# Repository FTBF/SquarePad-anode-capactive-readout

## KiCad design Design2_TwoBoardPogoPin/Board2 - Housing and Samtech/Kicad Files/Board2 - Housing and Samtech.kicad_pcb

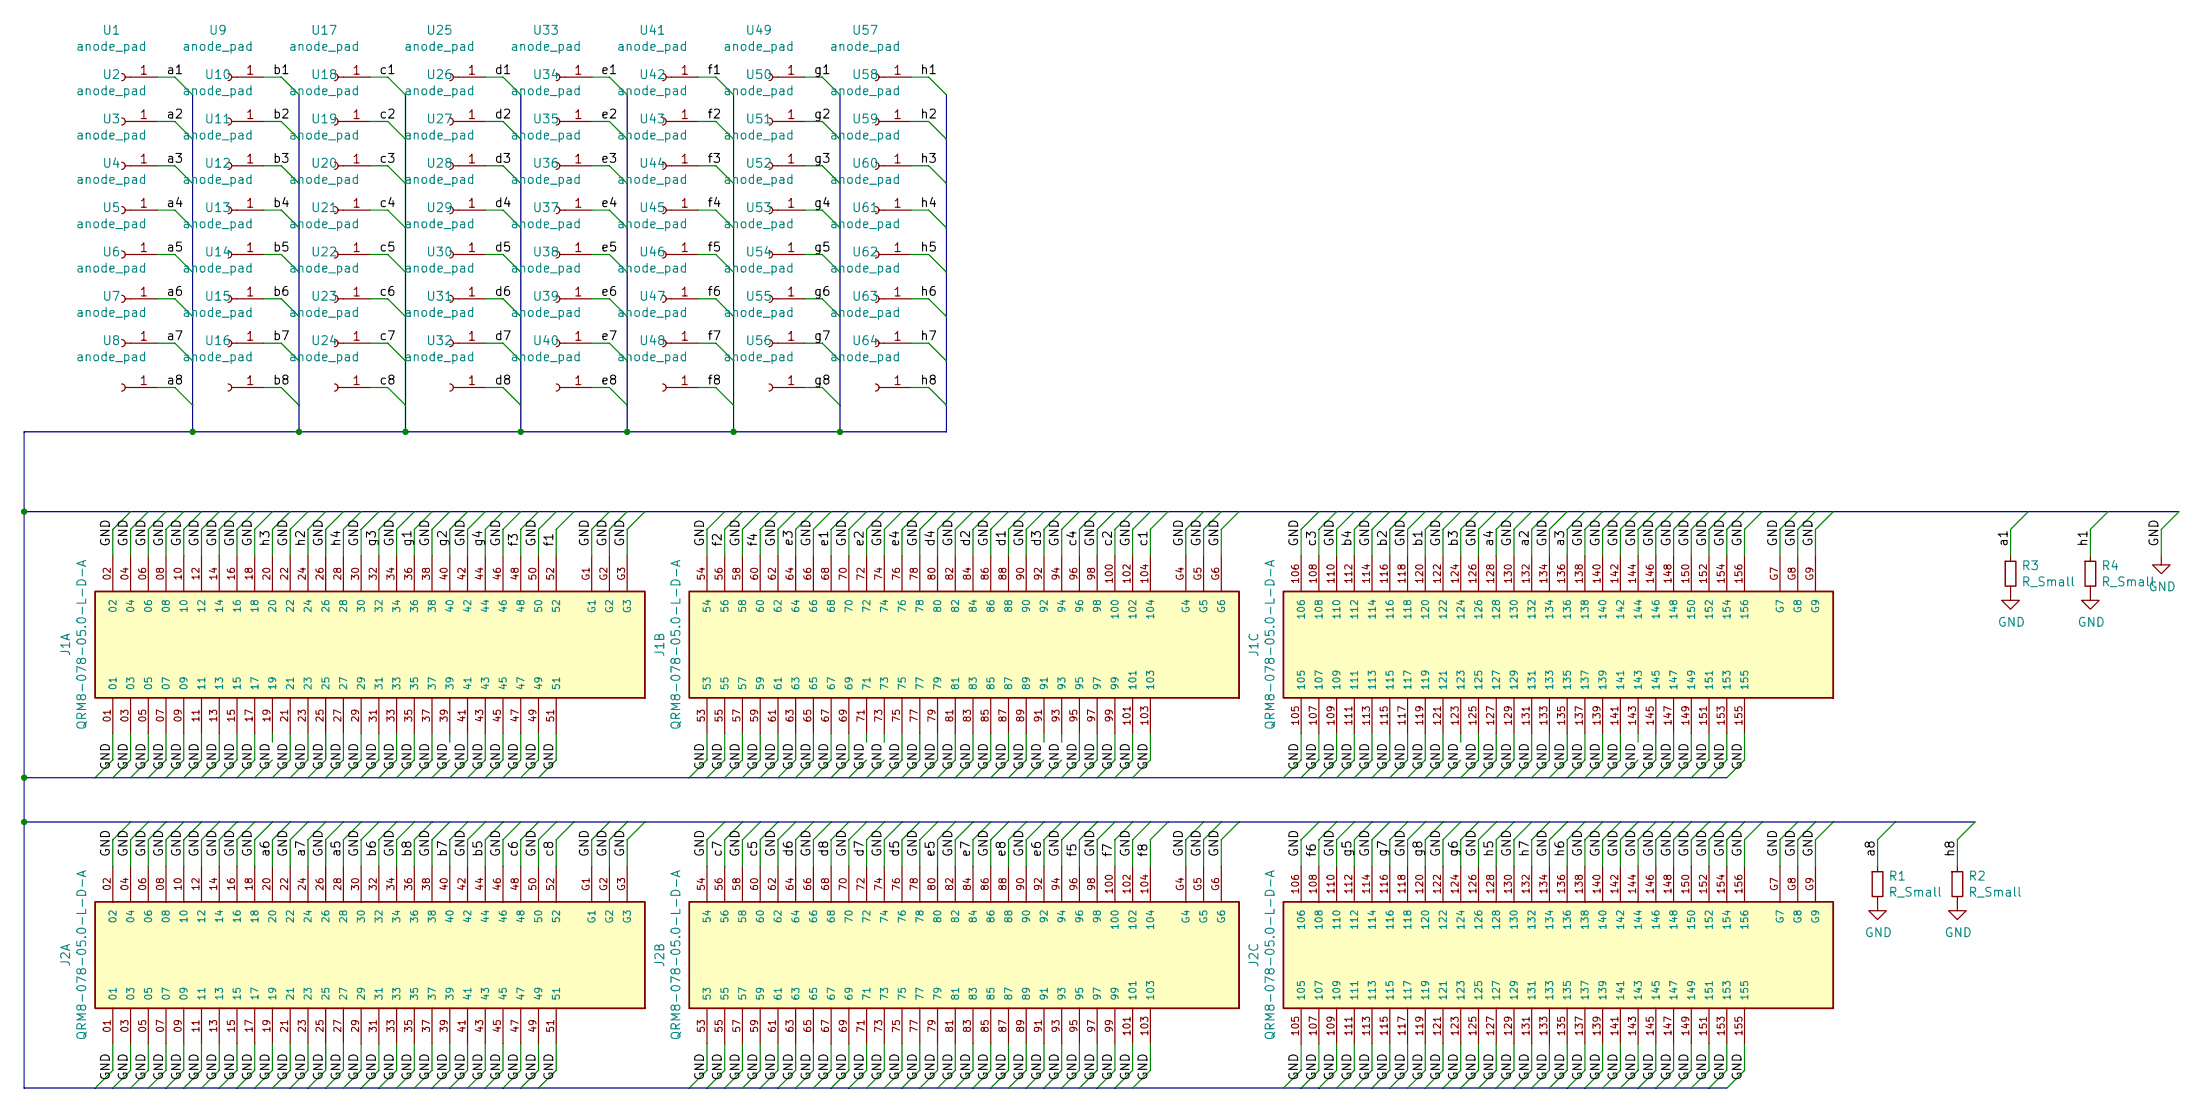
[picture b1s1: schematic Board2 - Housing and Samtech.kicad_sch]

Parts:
J1, J2: QRM8-078-05.0-L-D-A; SAMTEC_QRM8-078-05.0-L-D-A
R1, R2, R3, R4: R_Small; R_0805_2012Metric_Pad1.20x1.40mm_HandSolder
U1, U2, U3, U4, U5, U6, U7, U8, U9, U10, U11, U12, U13, U14, U15, U16, U17, U18, U19, U20, U21, U22, U23, U24, U25, U26, U27, U28, U29, U30, U31, U32, U33, U34, U35, U36, U37, U38, U39, U40, U41, U42, U43, U44, U45, U46, U47, U48, U49, U50, U51, U52, U53, U54, U55, U56, U57, U58, U59, U60, U61, U62, U63, U64: anode_pad; Pin_D0.7mm_L6.5mm_W1.8mm_FlatFork

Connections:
/a1: R3.1, U1.1
/a2: J1.132, U2.1
/a3: J1.136, U3.1
/a4: J1.128, U4.1
/a5: J2.28, U5.1
/a6: J2.20, U6.1
/a7: J2.24, U7.1
/a8: R1.1, U8.1
/b1: J1.120, U9.1
/b2: J1.116, U10.1
/b3: J1.124, U11.1
/b4: J1.112, U12.1
/b5: J2.44, U13.1
/b6: J2.32, U14.1
/b7: J2.40, U15.1
/b8: J2.36, U16.1
/c1: J1.104, U17.1
/c2: J1.100, U18.1
/c3: J1.108, U19.1
/c4: J1.96, U20.1
/c5: J2.60, U21.1
/c6: J2.48, U22.1
/c7: J2.56, U23.1
/c8: J2.52, U24.1
/d1: J1.88, U25.1
/d2: J1.84, U26.1
/d3: J1.92, U27.1
/d4: J1.80, U28.1
/d5: J2.76, U29.1
/d6: J2.64, U30.1
/d7: J2.72, U31.1
/d8: J2.68, U32.1
/e1: J1.68, U33.1
/e2: J1.72, U34.1
/e3: J1.64, U35.1
/e4: J1.76, U36.1
/e5: J2.80, U37.1
/e6: J2.92, U38.1
/e7: J2.84, U39.1
/e8: J2.88, U40.1
/f1: J1.52, U41.1
/f2: J1.56, U42.1
/f3: J1.48, U43.1
/f4: J1.60, U44.1
/f5: J2.96, U45.1
/f6: J2.108, U46.1
/f7: J2.100, U47.1
/f8: J2.104, U48.1
/g1: J1.36, U49.1
/g2: J1.40, U50.1
/g3: J1.32, U51.1
/g4: J1.44, U52.1
/g5: J2.112, U53.1
/g6: J2.124, U54.1
/g7: J2.116, U55.1
/g8: J2.120, U56.1
/h1: R4.1, U57.1
/h2: J1.24, U58.1
/h3: J1.20, U59.1
/h4: J1.28, U60.1
/h5: J2.128, U61.1
/h6: J2.136, U62.1
/h7: J2.132, U63.1
/h8: R2.1, U64.1
GND: J1.01, J1.02, J1.03, J1.04, J1.05, J1.06, J1.07, J1.08, J1.09, J1.10, J1.11, J1.12, J1.13, J1.14, J1.15, J1.16, J1.17, J1.18, J1.19, J1.21, J1.22, J1.23, J1.25, J1.26, J1.27, J1.29, J1.30, J1.31, J1.33, J1.34, J1.35, J1.37, J1.38, J1.39, J1.41, J1.42, J1.43, J1.45, J1.46, J1.47, J1.49, J1.50, J1.51, J1.53, J1.54, J1.55, J1.57, J1.58, J1.59, J1.61, J1.62, J1.63, J1.65, J1.66, J1.67, J1.69, J1.70, J1.71, J1.73, J1.74, J1.75, J1.77, J1.78, J1.79, J1.81, J1.82, J1.83, J1.85, J1.86, J1.87, J1.89, J1.90, J1.91, J1.93, J1.94, J1.95, J1.97, J1.98, J1.99, J1.101, J1.102, J1.103, J1.105, J1.106, J1.107, J1.109, J1.110, J1.111, J1.113, J1.114, J1.115, J1.117, J1.118, J1.119, J1.121, J1.122, J1.123, J1.125, J1.126, J1.127, J1.129, J1.130, J1.131, J1.133, J1.134, J1.135, J1.137, J1.138, J1.139, J1.140, J1.141, J1.142, J1.143, J1.144, J1.145, J1.146, J1.147, J1.148, J1.149, J1.150, J1.151, J1.152, J1.153, J1.154, J1.155, J1.156, J1.G1, J1.G2, J1.G3, J1.G4, J1.G5, J1.G6, J1.G7, J1.G8, J1.G9, J2.01, J2.02, J2.03, J2.04, J2.05, J2.06, J2.07, J2.08, J2.09, J2.10, J2.11, J2.12, J2.13, J2.14, J2.15, J2.16, J2.17, J2.18, J2.19, J2.21, J2.22, J2.23, J2.25, J2.26, J2.27, J2.29, J2.30, J2.31, J2.33, J2.34, J2.35, J2.37, J2.38, J2.39, J2.41, J2.42, J2.43, J2.45, J2.46, J2.47, J2.49, J2.50, J2.51, J2.53, J2.54, J2.55, J2.57, J2.58, J2.59, J2.61, J2.62, J2.63, J2.65, J2.66, J2.67, J2.69, J2.70, J2.71, J2.73, J2.74, J2.75, J2.77, J2.78, J2.79, J2.81, J2.82, J2.83, J2.85, J2.86, J2.87, J2.89, J2.90, J2.91, J2.93, J2.94, J2.95, J2.97, J2.98, J2.99, J2.101, J2.102, J2.103, J2.105, J2.106, J2.107, J2.109, J2.110, J2.111, J2.113, J2.114, J2.115, J2.117, J2.118, J2.119, J2.121, J2.122, J2.123, J2.125, J2.126, J2.127, J2.129, J2.130, J2.131, J2.133, J2.134, J2.135, J2.137, J2.138, J2.139, J2.140, J2.141, J2.142, J2.143, J2.144, J2.145, J2.146, J2.147, J2.148, J2.149, J2.150, J2.151, J2.152, J2.153, J2.154, J2.155, J2.156, J2.G1, J2.G2, J2.G3, J2.G4, J2.G5, J2.G6, J2.G7, J2.G8, J2.G9, R1.2, R2.2, R3.2, R4.2

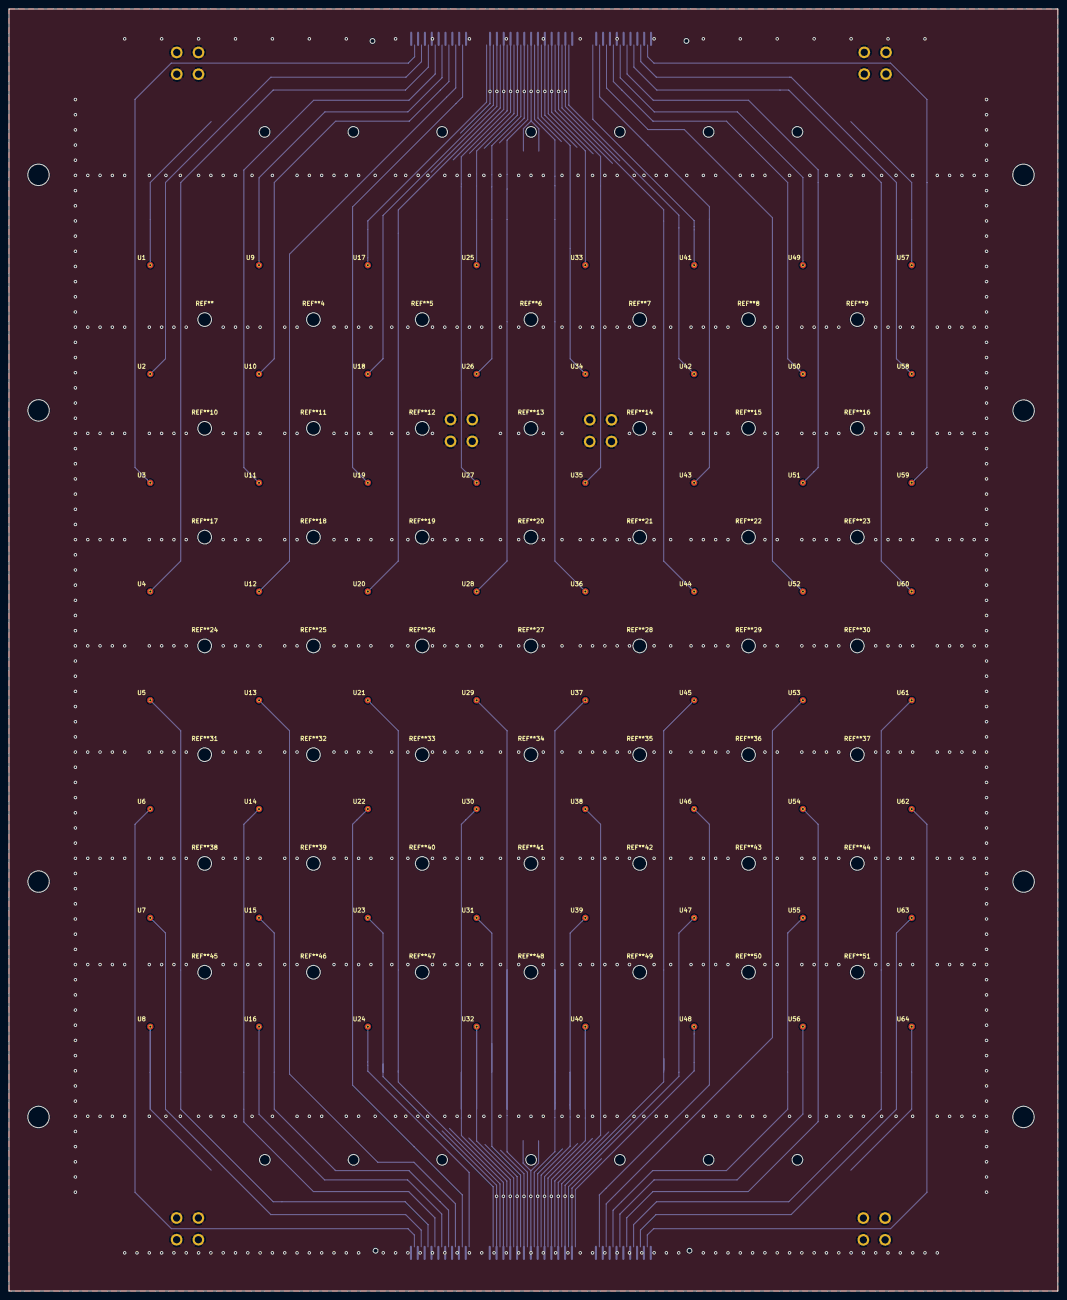
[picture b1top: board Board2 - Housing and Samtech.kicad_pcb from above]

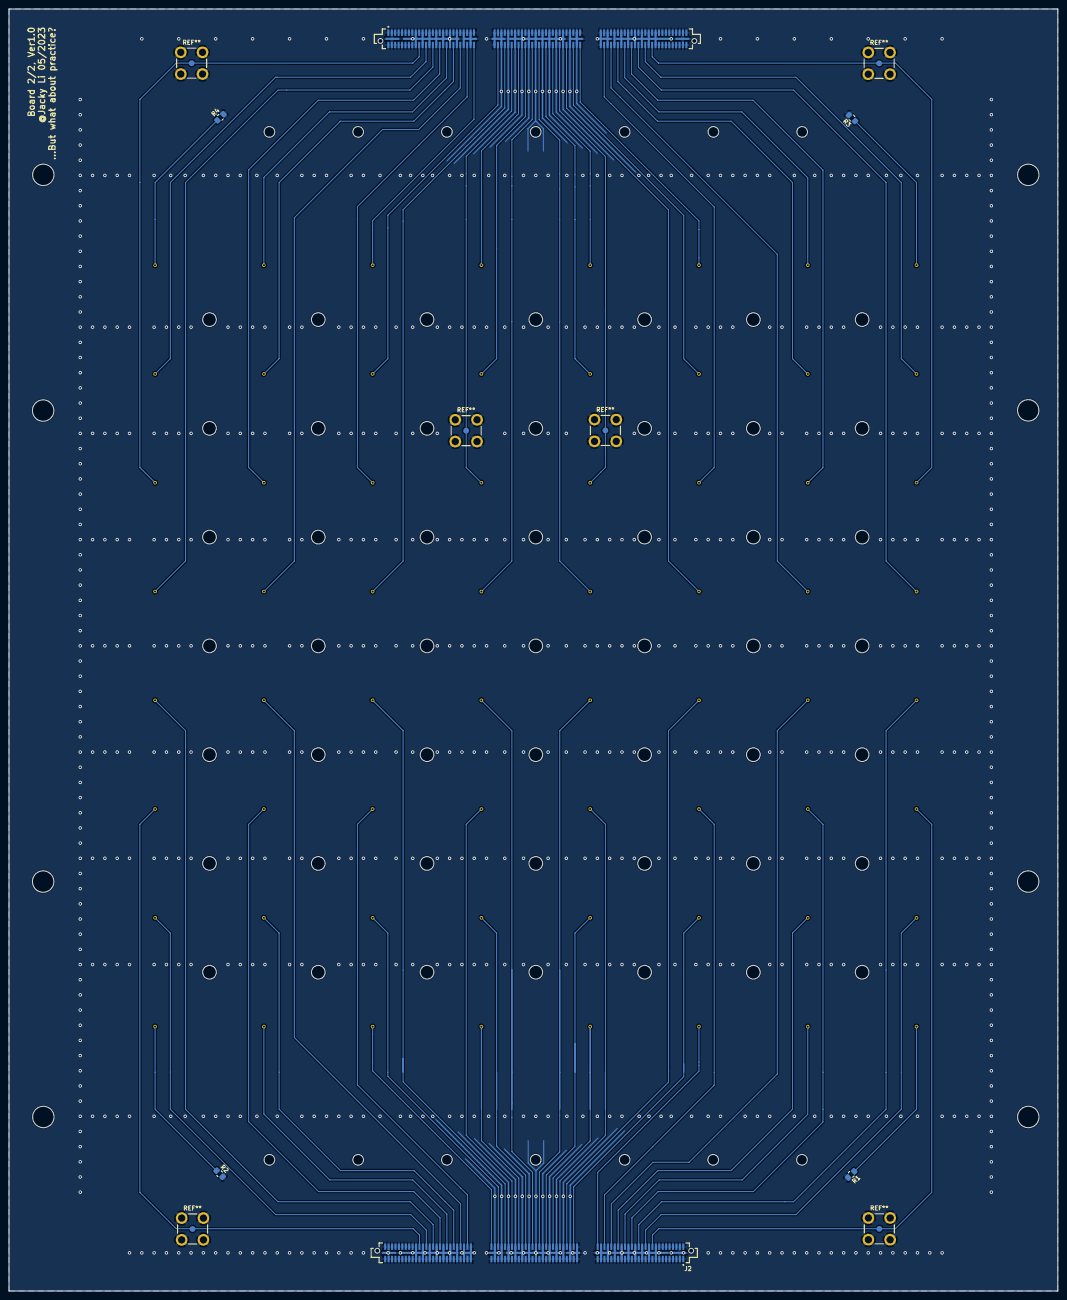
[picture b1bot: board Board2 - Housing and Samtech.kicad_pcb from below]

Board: 4 copper layers, 244.9 x 299.4 mm, 70 parts (6 on the bottom side), 65 nets.

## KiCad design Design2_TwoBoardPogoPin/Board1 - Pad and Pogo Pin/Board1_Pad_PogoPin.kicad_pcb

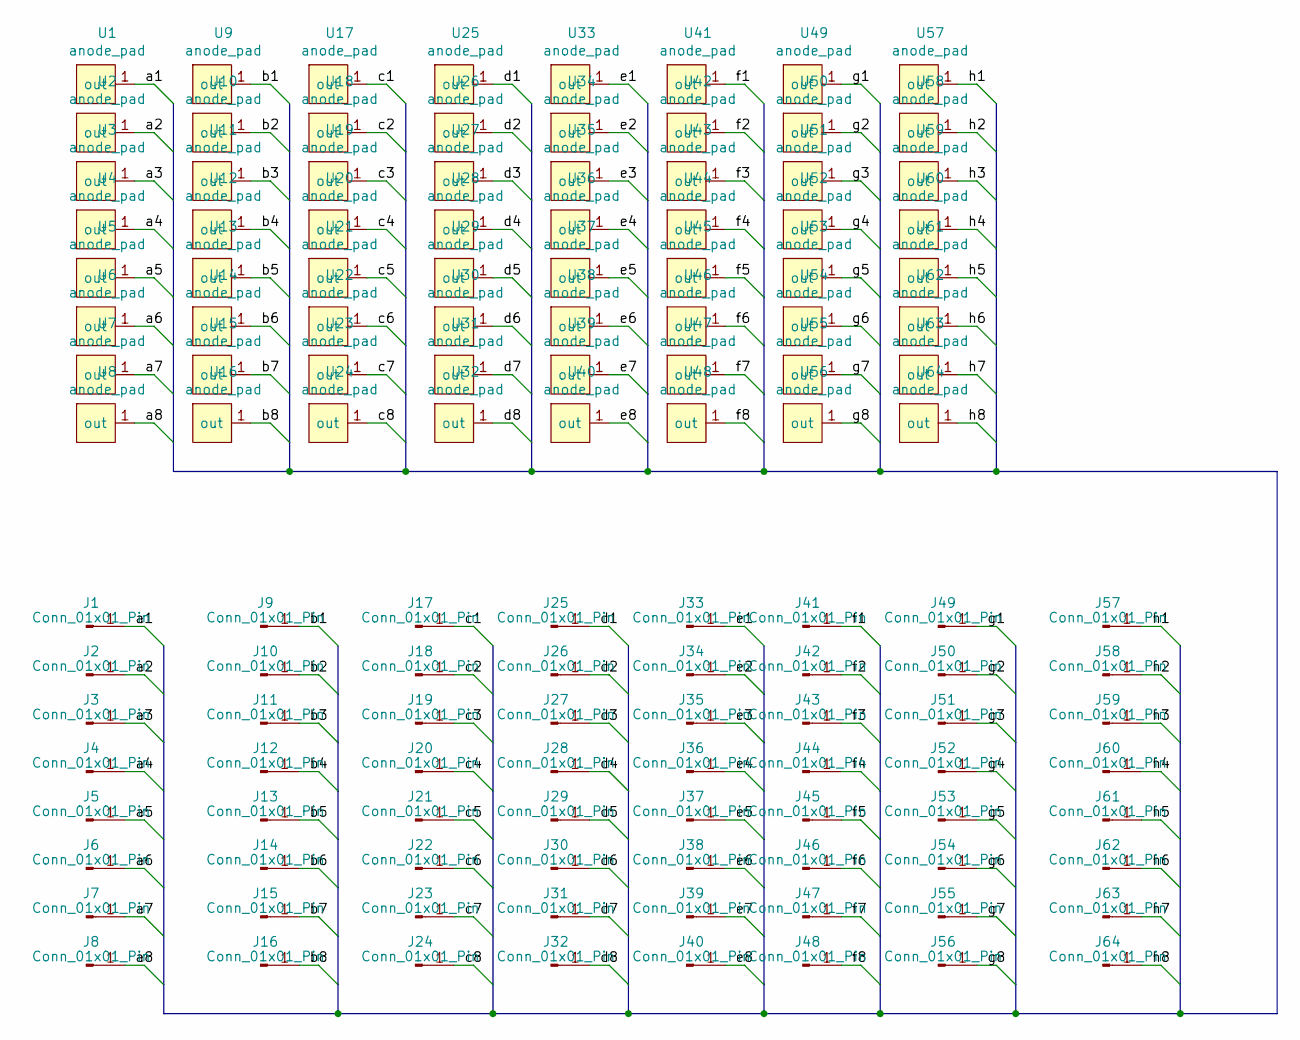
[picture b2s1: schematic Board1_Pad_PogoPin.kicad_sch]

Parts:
J1, J2, J3, J4, J5, J6, J7, J8, J9, J10, J11, J12, J13, J14, J15, J16, J17, J18, J19, J20, J21, J22, J23, J24, J25, J26, J27, J28, J29, J30, J31, J32, J33, J34, J35, J36, J37, J38, J39, J40, J41, J42, J43, J44, J45, J46, J47, J48, J49, J50, J51, J52, J53, J54, J55, J56, J57, J58, J59, J60, J61, J62, J63, J64: Conn_01x01_Pin; PogoPinWithTail
U1, U2, U3, U4, U5, U6, U7, U8, U9, U10, U11, U12, U13, U14, U15, U16, U17, U18, U19, U20, U21, U22, U23, U24, U25, U26, U27, U28, U29, U30, U31, U32, U33, U34, U35, U36, U37, U38, U39, U40, U41, U42, U43, U44, U45, U46, U47, U48, U49, U50, U51, U52, U53, U54, U55, U56, U57, U58, U59, U60, U61, U62, U63, U64: anode_pad; anode_square_pad_no_hole

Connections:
/a1: J1.1, U1.1 (out)
/a2: J2.1, U2.1 (out)
/a3: J3.1, U3.1 (out)
/a4: J4.1, U4.1 (out)
/a5: J5.1, U5.1 (out)
/a6: J6.1, U6.1 (out)
/a7: J7.1, U7.1 (out)
/a8: J8.1, U8.1 (out)
/b1: J9.1, U9.1 (out)
/b2: J10.1, U10.1 (out)
/b3: J11.1, U11.1 (out)
/b4: J12.1, U12.1 (out)
/b5: J13.1, U13.1 (out)
/b6: J14.1, U14.1 (out)
/b7: J15.1, U15.1 (out)
/b8: J16.1, U16.1 (out)
/c1: J17.1, U17.1 (out)
/c2: J18.1, U18.1 (out)
/c3: J19.1, U19.1 (out)
/c4: J20.1, U20.1 (out)
/c5: J21.1, U21.1 (out)
/c6: J22.1, U22.1 (out)
/c7: J23.1, U23.1 (out)
/c8: J24.1, U24.1 (out)
/d1: J25.1, U25.1 (out)
/d2: J26.1, U26.1 (out)
/d3: J27.1, U27.1 (out)
/d4: J28.1, U28.1 (out)
/d5: J29.1, U29.1 (out)
/d6: J30.1, U30.1 (out)
/d7: J31.1, U31.1 (out)
/d8: J32.1, U32.1 (out)
/e1: J33.1, U33.1 (out)
/e2: J34.1, U34.1 (out)
/e3: J35.1, U35.1 (out)
/e4: J36.1, U36.1 (out)
/e5: J37.1, U37.1 (out)
/e6: J38.1, U38.1 (out)
/e7: J39.1, U39.1 (out)
/e8: J40.1, U40.1 (out)
/f1: J41.1, U41.1 (out)
/f2: J42.1, U42.1 (out)
/f3: J43.1, U43.1 (out)
/f4: J44.1, U44.1 (out)
/f5: J45.1, U45.1 (out)
/f6: J46.1, U46.1 (out)
/f7: J47.1, U47.1 (out)
/f8: J48.1, U48.1 (out)
/g1: J49.1, U49.1 (out)
/g2: J50.1, U50.1 (out)
/g3: J51.1, U51.1 (out)
/g4: J52.1, U52.1 (out)
/g5: J53.1, U53.1 (out)
/g6: J54.1, U54.1 (out)
/g7: J55.1, U55.1 (out)
/g8: J56.1, U56.1 (out)
/h1: J57.1, U57.1 (out)
/h2: J58.1, U58.1 (out)
/h3: J59.1, U59.1 (out)
/h4: J60.1, U60.1 (out)
/h5: J61.1, U61.1 (out)
/h6: J62.1, U62.1 (out)
/h7: J63.1, U63.1 (out)
/h8: J64.1, U64.1 (out)

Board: 2 copper layers, 128 parts (64 on the bottom side), 64 nets, no tracks yet.

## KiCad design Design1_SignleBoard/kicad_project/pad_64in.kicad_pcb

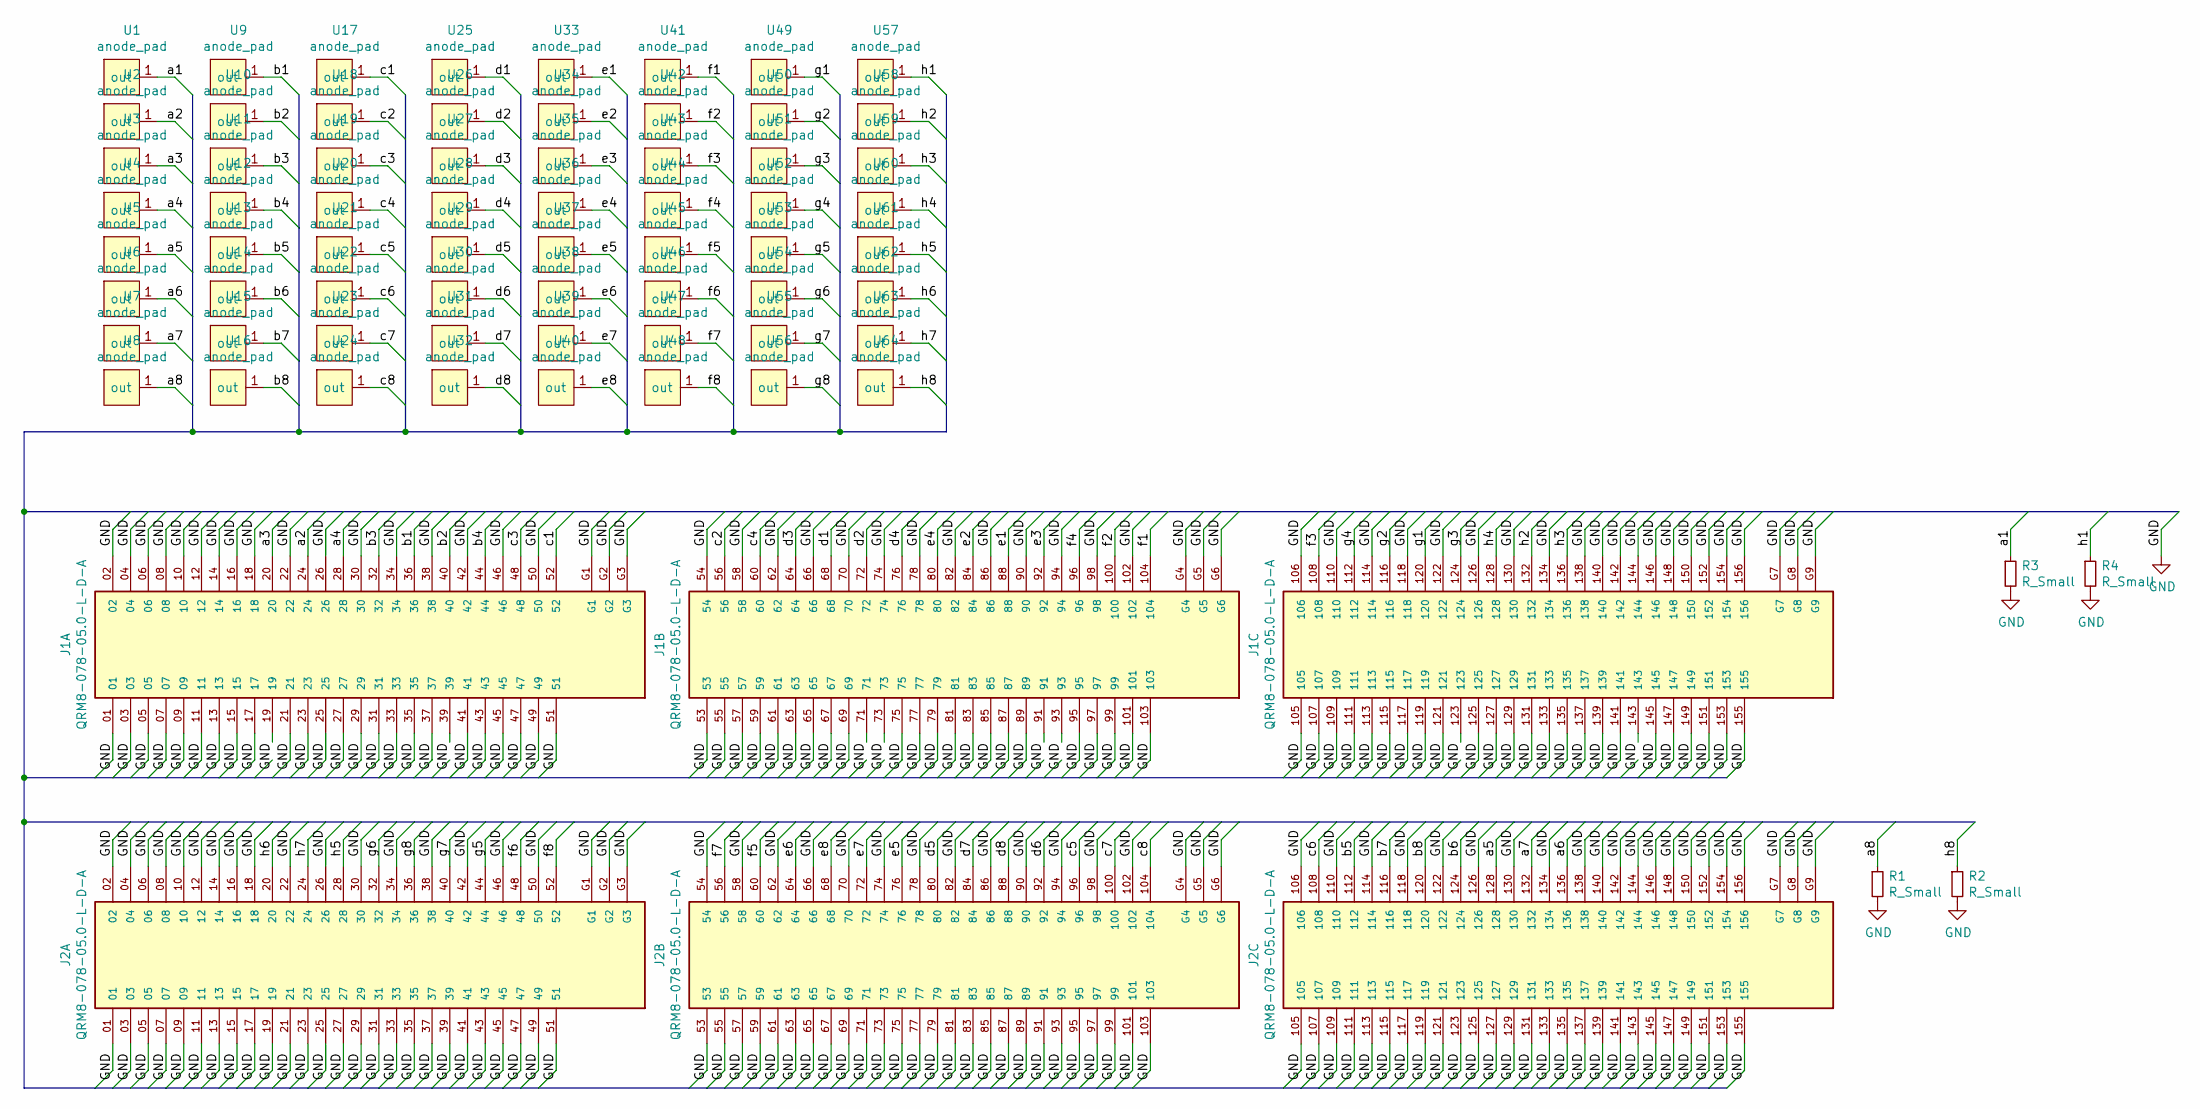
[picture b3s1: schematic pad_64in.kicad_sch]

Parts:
J1, J2: QRM8-078-05.0-L-D-A; SAMTEC_QRM8-078-05.0-L-D-A
R1, R2, R3, R4: R_Small; R_0805_2012Metric_Pad1.15x1.40mm_HandSolder
U1, U2, U3, U4, U5, U6, U7, U8, U9, U10, U11, U12, U13, U14, U15, U16, U17, U18, U19, U20, U21, U22, U23, U24, U25, U26, U27, U28, U29, U30, U31, U32, U33, U34, U35, U36, U37, U38, U39, U40, U41, U42, U43, U44, U45, U46, U47, U48, U49, U50, U51, U52, U53, U54, U55, U56, U57, U58, U59, U60, U61, U62, U63, U64: anode_pad; anode_square_pad

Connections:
/a1: R3.1, U1.1
/a2: J1.24, U2.1
/a3: J1.20, U3.1
/a4: J1.28, U4.1
/a5: J2.128, U5.1
/a6: J2.136, U6.1
/a7: J2.132, U7.1
/a8: R1.1, U8.1
/b1: J1.36, U9.1
/b2: J1.40, U10.1
/b3: J1.32, U11.1
/b4: J1.44, U12.1
/b5: J2.112, U13.1
/b6: J2.124, U14.1
/b7: J2.116, U15.1
/b8: J2.120, U16.1
/c1: J1.52, U17.1
/c2: J1.56, U18.1
/c3: J1.48, U19.1
/c4: J1.60, U20.1
/c5: J2.96, U21.1
/c6: J2.108, U22.1
/c7: J2.100, U23.1
/c8: J2.104, U24.1
/d1: J1.68, U25.1
/d2: J1.72, U26.1
/d3: J1.64, U27.1
/d4: J1.76, U28.1
/d5: J2.80, U29.1
/d6: J2.92, U30.1
/d7: J2.84, U31.1
/d8: J2.88, U32.1
/e1: J1.88, U33.1
/e2: J1.84, U34.1
/e3: J1.92, U35.1
/e4: J1.80, U36.1
/e5: J2.76, U37.1
/e6: J2.64, U38.1
/e7: J2.72, U39.1
/e8: J2.68, U40.1
/f1: J1.104, U41.1
/f2: J1.100, U42.1
/f3: J1.108, U43.1
/f4: J1.96, U44.1
/f5: J2.60, U45.1
/f6: J2.48, U46.1
/f7: J2.56, U47.1
/f8: J2.52, U48.1
/g1: J1.120, U49.1
/g2: J1.116, U50.1
/g3: J1.124, U51.1
/g4: J1.112, U52.1
/g5: J2.44, U53.1
/g6: J2.32, U54.1
/g7: J2.40, U55.1
/g8: J2.36, U56.1
/h1: R4.1, U57.1
/h2: J1.132, U58.1
/h3: J1.136, U59.1
/h4: J1.128, U60.1
/h5: J2.28, U61.1
/h6: J2.20, U62.1
/h7: J2.24, U63.1
/h8: R2.1, U64.1
GND: J1.01, J1.02, J1.03, J1.04, J1.05, J1.06, J1.07, J1.08, J1.09, J1.10, J1.11, J1.12, J1.13, J1.14, J1.15, J1.16, J1.17, J1.18, J1.19, J1.21, J1.22, J1.23, J1.25, J1.26, J1.27, J1.29, J1.30, J1.31, J1.33, J1.34, J1.35, J1.37, J1.38, J1.39, J1.41, J1.42, J1.43, J1.45, J1.46, J1.47, J1.49, J1.50, J1.51, J1.53, J1.54, J1.55, J1.57, J1.58, J1.59, J1.61, J1.62, J1.63, J1.65, J1.66, J1.67, J1.69, J1.70, J1.71, J1.73, J1.74, J1.75, J1.77, J1.78, J1.79, J1.81, J1.82, J1.83, J1.85, J1.86, J1.87, J1.89, J1.90, J1.91, J1.93, J1.94, J1.95, J1.97, J1.98, J1.99, J1.101, J1.102, J1.103, J1.105, J1.106, J1.107, J1.109, J1.110, J1.111, J1.113, J1.114, J1.115, J1.117, J1.118, J1.119, J1.121, J1.122, J1.123, J1.125, J1.126, J1.127, J1.129, J1.130, J1.131, J1.133, J1.134, J1.135, J1.137, J1.138, J1.139, J1.140, J1.141, J1.142, J1.143, J1.144, J1.145, J1.146, J1.147, J1.148, J1.149, J1.150, J1.151, J1.152, J1.153, J1.154, J1.155, J1.156, J1.G1, J1.G2, J1.G3, J1.G4, J1.G5, J1.G6, J1.G7, J1.G8, J1.G9, J2.01, J2.02, J2.03, J2.04, J2.05, J2.06, J2.07, J2.08, J2.09, J2.10, J2.11, J2.12, J2.13, J2.14, J2.15, J2.16, J2.17, J2.18, J2.19, J2.21, J2.22, J2.23, J2.25, J2.26, J2.27, J2.29, J2.30, J2.31, J2.33, J2.34, J2.35, J2.37, J2.38, J2.39, J2.41, J2.42, J2.43, J2.45, J2.46, J2.47, J2.49, J2.50, J2.51, J2.53, J2.54, J2.55, J2.57, J2.58, J2.59, J2.61, J2.62, J2.63, J2.65, J2.66, J2.67, J2.69, J2.70, J2.71, J2.73, J2.74, J2.75, J2.77, J2.78, J2.79, J2.81, J2.82, J2.83, J2.85, J2.86, J2.87, J2.89, J2.90, J2.91, J2.93, J2.94, J2.95, J2.97, J2.98, J2.99, J2.101, J2.102, J2.103, J2.105, J2.106, J2.107, J2.109, J2.110, J2.111, J2.113, J2.114, J2.115, J2.117, J2.118, J2.119, J2.121, J2.122, J2.123, J2.125, J2.126, J2.127, J2.129, J2.130, J2.131, J2.133, J2.134, J2.135, J2.137, J2.138, J2.139, J2.140, J2.141, J2.142, J2.143, J2.144, J2.145, J2.146, J2.147, J2.148, J2.149, J2.150, J2.151, J2.152, J2.153, J2.154, J2.155, J2.156, J2.G1, J2.G2, J2.G3, J2.G4, J2.G5, J2.G6, J2.G7, J2.G8, J2.G9, R1.2, R2.2, R3.2, R4.2

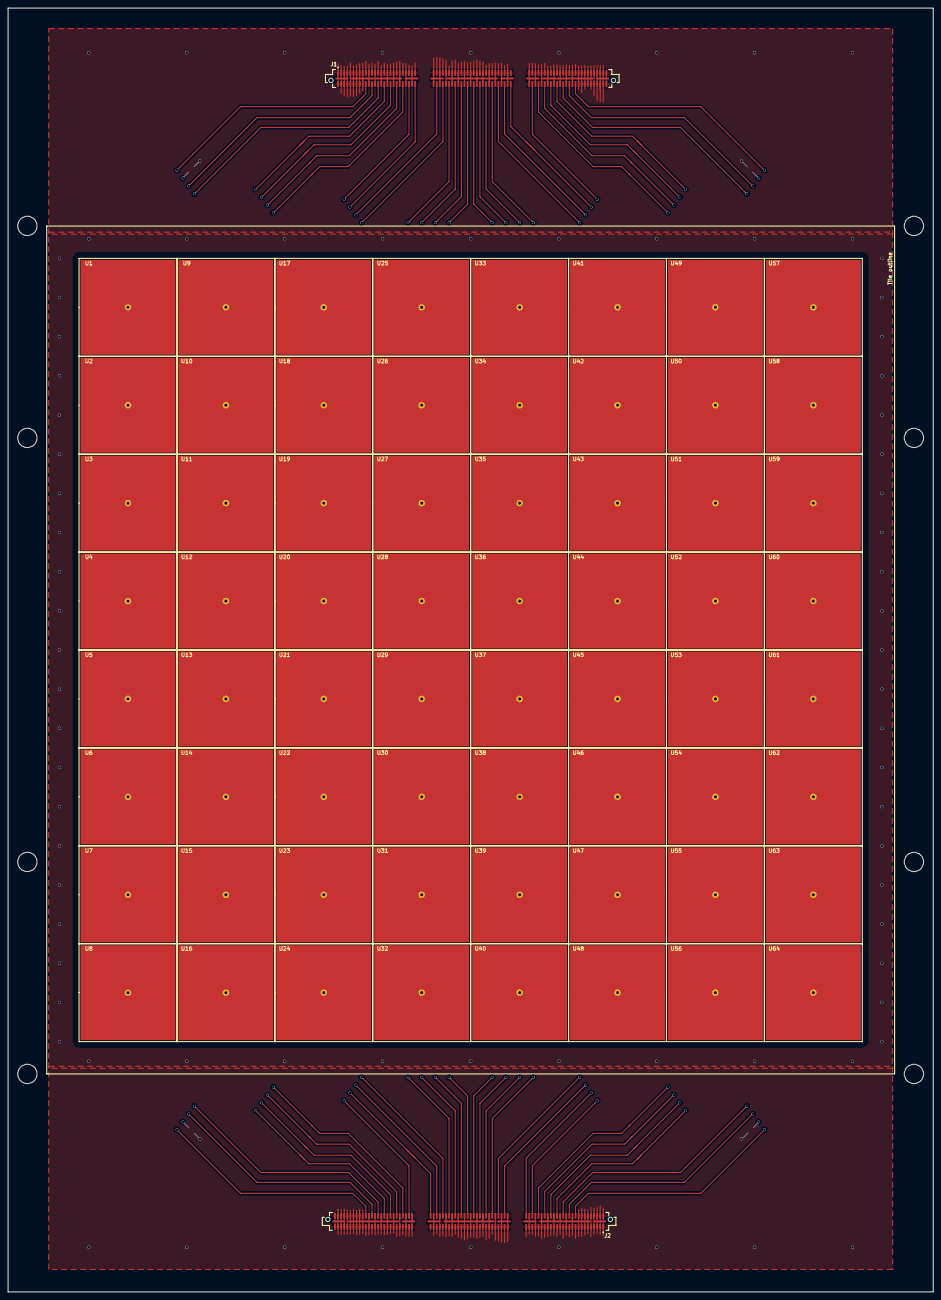
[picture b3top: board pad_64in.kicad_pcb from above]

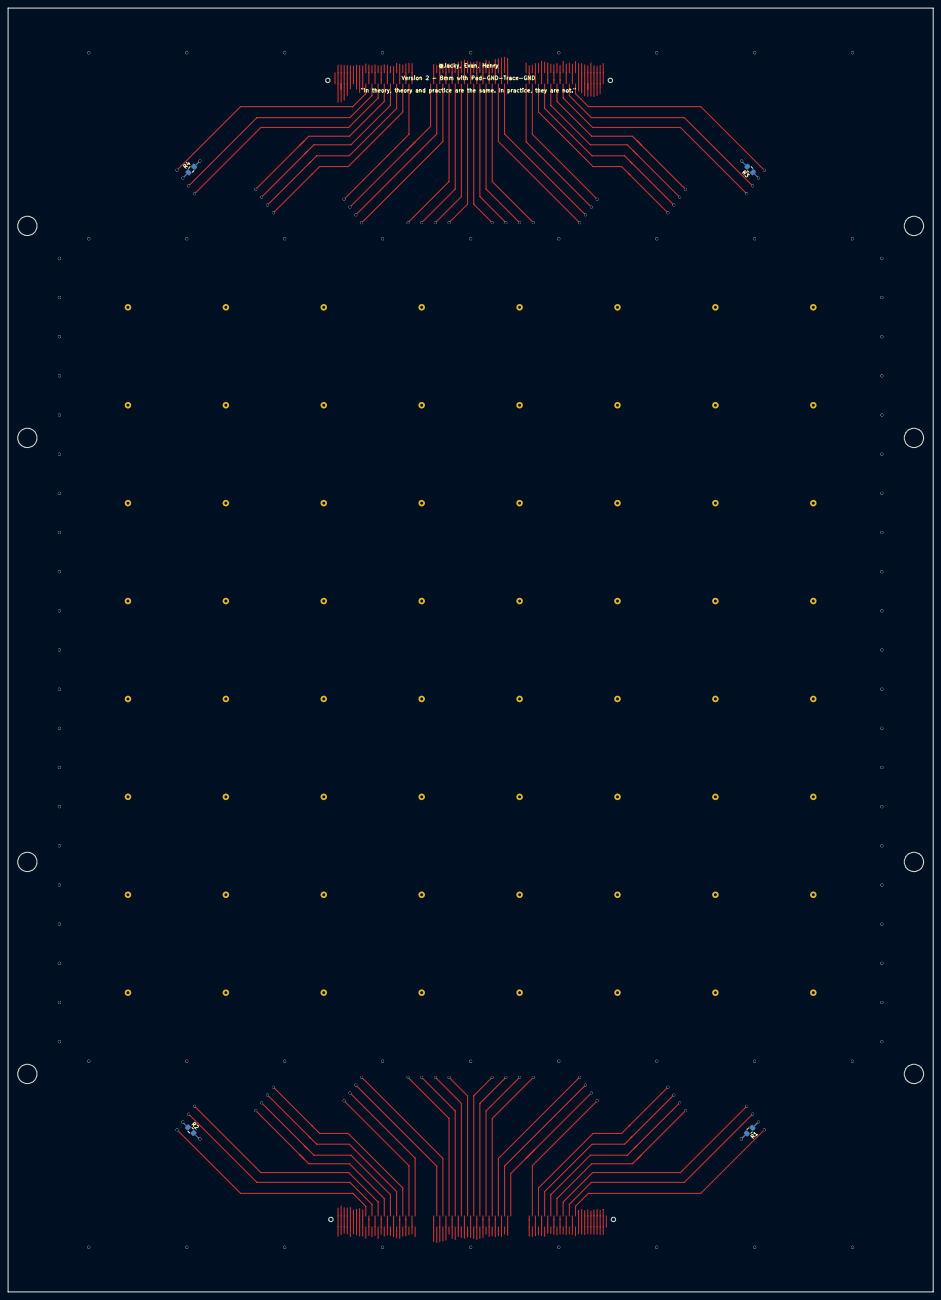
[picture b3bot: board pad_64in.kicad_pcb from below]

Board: 6 copper layers, 240.0 x 333.1 mm, 70 parts (4 on the bottom side), 65 nets.

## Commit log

2023-01-13 Still need to correct monting holes
2023-03-02 submiting design2
2023-03-03 two boards finished
2023-03-18 Finished two board design, waiting for review
2023-03-19 update step files
2023-05-12 May 12 update
2023-05-22 ready for fab
